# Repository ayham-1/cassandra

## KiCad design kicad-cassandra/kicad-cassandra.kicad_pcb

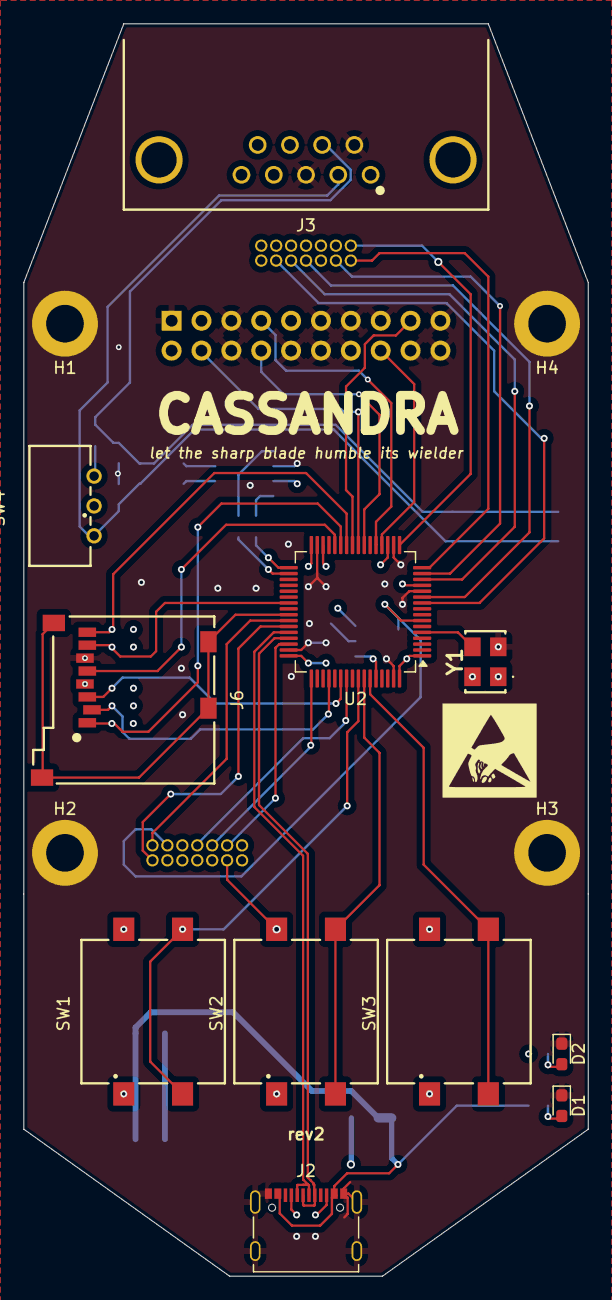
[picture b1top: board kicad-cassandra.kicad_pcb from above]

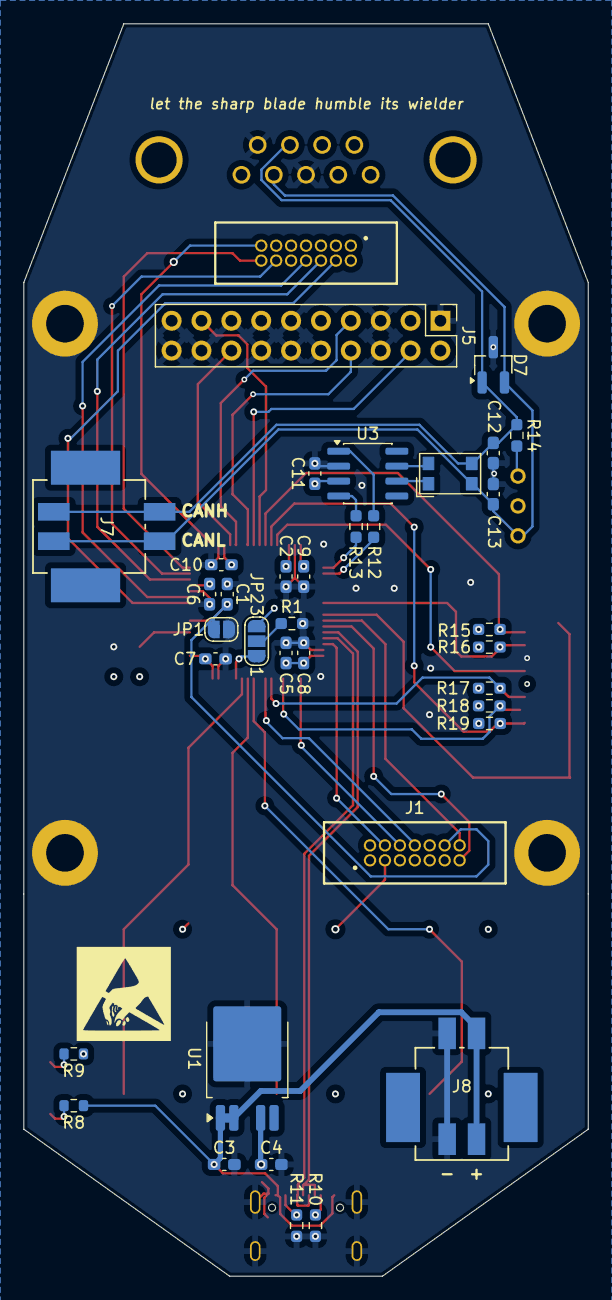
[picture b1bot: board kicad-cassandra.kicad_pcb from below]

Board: 4 copper layers, 48.0 x 106.5 mm, 52 parts (37 on the bottom side), 49 nets.

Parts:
C1, C6, C7, C8, C9, C10, C11: 100n; C_0603_1608Metric_Pad1.08x0.95mm_HandSolder
C2: 2.2u; C_0603_1608Metric_Pad1.08x0.95mm_HandSolder
C3: 1u; C_0603_1608Metric_Pad1.08x0.95mm_HandSolder
C4, C5: 4.7u; C_0603_1608Metric_Pad1.08x0.95mm_HandSolder
C12, C13: 10p; C_0603_1608Metric_Pad1.08x0.95mm_HandSolder
D1, D2: RED; LED_0603_1608Metric_Pad1.05x0.95mm_HandSolder
D7: SZNUP2105L; SOT-23_Handsoldering
H1, H2, H3, H4: MountingHole_Pad; MountingHole_3.2mm_M3_DIN965_Pad
J1, J4: Conn_ST_STDC14; ST_Link_Connection
J2: USB_C_Receptacle_USB2.0_16P; USB_C_Receptacle_Palconn_UTC16-G
J3: DE9_Pins_MountingHoles; WE-D-SUB_THT90_EC_210112013
J5: Conn_02x10_Odd_Even; PinHeader_2x10_P2.54mm_Vertical
J6: Micro_SD_Card_Det1; 693071010811
J7, J8: CONN4_05010302_WRE
JP1: SolderJumper_2_Open; SolderJumper-2_P1.3mm_Open_RoundedPad1.0x1.5mm
JP2: SolderJumper_3_Open; SolderJumper-3_P1.3mm_Open_RoundedPad1.0x1.5mm_NumberLabels
L1: 744235510; L_CommonModeChoke_Coilcraft_1812CAN
R1, R15, R16, R17, R18, R19: 10k; R_0603_1608Metric_Pad0.98x0.95mm_HandSolder
R8: 330; R_0603_1608Metric
R9: 230; R_0603_1608Metric
R10, R11: 5.1k; R_0603_1608Metric_Pad0.98x0.95mm_HandSolder
R12, R13: 4.7k; R_0603_1608Metric_Pad0.98x0.95mm_HandSolder
R14: 120; R_0603_1608Metric_Pad0.98x0.95mm_HandSolder
SW1, SW2, SW3: SW_Push; 430162073826
SW4: SW_SPDT; 450302014072
U1: BD33FC0WFP; TO-252-4
U2: STM32F446RETx; LQFP-64_10x10mm_P0.5mm
U3: SN65HVD232; SOIC-8_3.9x4.9mm_P1.27mm
Y1: 831024589

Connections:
+3.3V: C4.1, C5.1, C6.1, C7.1, C8.1, C9.1, C10.1, C11.1, J1.3 (VCC), J5.2, J6.4 (VDD), JP2.3 (B), R9.1, R15.1, R16.1, R17.1, R18.1, R19.1, SW1.1, SW2.1, SW3.1, U1.4 (VO), U2.1 (VBAT), U2.13 (VDDA), U2.19 (VDD), U2.32 (VDD), U2.48 (VDD), U2.64 (VDD), U3.3 (VCC), Y1.1 (ENABLE/DISABLE), Y1.4 (+VS)
/CAN/CAN_HIGH: C12.1, D7.1 (K), J3.7, J7.1, L1.3, R14.1
/CAN/CAN_LOW: C13.2, D7.2 (K), J3.2, J7.2, L1.2, SW4.2 (B)
/CAN/CAN_RX: R13.1, U2.33 (PB12)
/CAN/CAN_TX: R12.1, U2.34 (PB13)
/DISPLAY_ACTIVE_LOW_CHIP_SELECT: J5.17, U2.25 (PC5)
/DISPLAY_ACTIVE_LOW_RESET: J5.16, U2.20 (PA4)
/DISPLAY_DC: J5.4, U2.24 (PC4)
/DISPLAY_SPI_SCLK: J5.7, U2.21 (PA5)
/DISPLAY_SPI_SDIN: J5.8, U2.23 (PA7)
/HOST_RST: C1.1, J1.12 (~RST), JP1.2 (B), U2.7 (NRST)
/HOST_SWCLK: J1.6 (JCLK/SWCLK), U2.49 (PA14)
/HOST_SWDIO: J1.4 (JTMS/SWDIO), U2.46 (PA13)
/HOST_SWO: J1.8 (JTDO/SWO), U2.55 (PB3)
/HOST_VCP_RX: J1.13 (VCP_RX), U2.43 (PA10)
/HOST_VCP_TX: J1.14 (VCP_TX), U2.42 (PA9)
/HSE: U2.5 (PH0), Y1.3 (OUTPUT)
/PBT_0: SW1.2, U2.57 (PB5)
/PBT_1: SW2.2, U2.58 (PB6)
/PBT_2: SW3.2, U2.59 (PB7)
/TGT_RST: J4.12 (~RST), U2.15 (PA1)
/TGT_SWCLK: J4.6 (JCLK/SWCLK), U2.14 (PA0)
/TGT_SWDIO: J4.4 (JTMS/SWDIO), U2.10 (PC2)
/TGT_SWO: J4.8 (JTDO/SWO), U2.11 (PC3)
/TGT_VCP_RX: J4.13 (VCP_RX), U2.17 (PA3)
/TGT_VCP_TX: J4.14 (VCP_TX), U2.16 (PA2)
/USB/USB_D+: J2.A6 (D+), J2.B6 (D+), U2.45 (PA12)
/USB/USB_D-: J2.A7 (D-), J2.B7 (D-), U2.44 (PA11)
/uSD_CLK: J6.5 (CLK), U2.28 (PB2)
/uSD_CMD: J6.3 (CMD), R17.2, U2.54 (PD2)
/uSD_D0: J6.7 (DAT0), R16.2, U2.39 (PC8)
/uSD_D1: J6.8 (DAT1), R15.2, U2.26 (PB0)
/uSD_D2: J6.1 (DAT2), R19.2, U2.27 (PB1)
/uSD_D3: J6.2 (DAT3/CD), R18.2, U2.52 (PC11)
/uSD_DET: J6.9 (DET_B), J6.10 (DET_A), U2.41 (PA8)
GND: C1.2, C2.2, C3.2, C4.2, C5.2, C6.2, C7.2, C8.2, C9.2, C10.2, C11.2, C12.2, C13.1, D1.1 (K), D2.1 (K), D7.3 (A), H1.1, H2.1, H3.1, H4.1, J1.5 (GND), J1.7 (GND), J1.11 (GNDDetect), J2.A1 (GND), J2.A12 (GND), J2.B1 (GND), J2.B12 (GND), J2.S1 (SHIELD), J3.3, J3.6, J4.5 (GND), J4.7 (GND), J4.11 (GNDDetect), J5.1, J5.5, J5.6, J5.10, J5.11, J5.12, J5.13, J5.14, J5.15, J5.18, J5.19, J5.20, J6.6 (VSS), J8.1, JP1.1 (A), R1.2, R10.2, R11.2, U1.3 (GND), U2.12 (VSSA), U2.18 (VSS), U2.31 (VSS), U2.47 (VSS), U2.63 (VSS), U3.2 (GND), Y1.2 (GND)
unnamed: D1.2 (A), R8.2
unnamed: D2.2 (A), R9.2
unnamed: J2.A5 (CC1), R10.1
unnamed: J2.B5 (CC2), R11.1
unnamed: JP2.1 (A), U2.60 (BOOT0)
unnamed: JP2.2 (C), R1.1
unnamed: R14.2, SW4.3 (C)
unnamed: C2.1, U2.30 (VCAP_1)
unnamed: L1.4, U3.7 (CANH)
unnamed: L1.1, U3.6 (CANL)
unnamed: R12.2, U3.1 (D)
unnamed: R13.2, U3.4 (R)
VDD: C3.1, J2.A4 (VBUS), J2.A9 (VBUS), J2.B4 (VBUS), J2.B9 (VBUS), J8.2, R8.1, U1.1 (EN), U1.2 (VCC)

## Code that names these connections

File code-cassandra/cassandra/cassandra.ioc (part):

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Mcu.Name=STM32F446R(C-E)Tx
Mcu.Package=LQFP64
Mcu.UserName=STM32F446RETx
PA0-WKUP.GPIOParameters=GPIO_Label
PA0-WKUP.GPIO_Label=TGT_SWCLK
PA0-WKUP.Signal=S_TIM2_CH1_ETR
PA1.GPIOParameters=GPIO_Label
PA1.GPIO_Label=TGT_RST
PA1.Signal=GPIO_Output
PA10.Mode=Asynchronous
PA10.Signal=USART1_RX
PA11.GPIOParameters=GPIO_PuPd
PA11.GPIO_PuPd=GPIO_PULLUP
PA11.Mode=Device_Only
PA11.Signal=USB_OTG_FS_DM
PA12.GPIOParameters=GPIO_PuPd
PA12.GPIO_PuPd=GPIO_PULLUP
PA12.Mode=Device_Only
PA12.Signal=USB_OTG_FS_DP
PA13.Mode=Serial_Wire
PA13.Signal=SYS_JTMS-SWDIO
PA14.Mode=Serial_Wire
PA14.Signal=SYS_JTCK-SWCLK
PA2.Mode=Asynchronous
PA2.Signal=USART2_TX
PA3.Mode=Asynchronous
PA3.Signal=USART2_RX
PA4.GPIOParameters=GPIO_PuPd,GPIO_Label
PA4.GPIO_Label=DISPLAY_ACTIVE_LOW_RESET
PA4.GPIO_PuPd=GPIO_PULLUP
PA4.Signal=GPIO_Output
PA5.Mode=Full_Duplex_Master
PA5.Signal=SPI1_SCK
PA6.Mode=Full_Duplex_Master
PA6.Signal=SPI1_MISO
PA7.Mode=Full_Duplex_Master
PA7.Signal=SPI1_MOSI
PA8.GPIOParameters=GPIO_Label
PA8.GPIO_Label=uSD_DET
PA8.Signal=GPIO_Input
PA9.Mode=Asynchronous
PA9.Signal=USART1_TX
PB0.GPIOParameters=GPIO_PuPd
PB0.GPIO_PuPd=GPIO_PULLUP
PB0.Mode=SD_4_bits_Wide_bus
PB0.Signal=SDIO_D1
PB1.GPIOParameters=GPIO_PuPd
PB1.GPIO_PuPd=GPIO_PULLUP
PB1.Mode=SD_4_bits_Wide_bus
PB1.Signal=SDIO_D2
PB12.GPIOParameters=GPIO_PuPd
PB12.GPIO_PuPd=GPIO_PULLUP
PB12.Mode=CAN_Activate
PB12.Signal=CAN2_RX
PB13.Mode=CAN_Activate
PB13.Signal=CAN2_TX
PB2.GPIOParameters=GPIO_PuPd
PB2.GPIO_PuPd=GPIO_NOPULL
PB2.Mode=SD_4_bits_Wide_bus
PB2.Signal=SDIO_CK
PB5.GPIOParameters=GPIO_PuPd,GPIO_Label,GPIO_ModeDefaultEXTI
PB5.GPIO_Label=PBT_0
PB5.GPIO_ModeDefaultEXTI=GPIO_MODE_IT_FALLING
PB5.GPIO_PuPd=GPIO_PULLDOWN
PB5.Signal=GPXTI5
PB6.GPIOParameters=GPIO_PuPd,GPIO_Label,GPIO_ModeDefaultEXTI
PB6.GPIO_Label=PBT_1
PB6.GPIO_ModeDefaultEXTI=GPIO_MODE_IT_FALLING
PB6.GPIO_PuPd=GPIO_PULLDOWN
PB6.Signal=GPXTI6
PB7.GPIOParameters=GPIO_PuPd,GPIO_Label
PB7.GPIO_Label=PBT_2
PB7.GPIO_PuPd=GPIO_PULLDOWN
PB7.Signal=GPXTI7
PC11.GPIOParameters=GPIO_PuPd
PC11.GPIO_PuPd=GPIO_PULLUP
PC11.Mode=SD_4_bits_Wide_bus
PC11.Signal=SDIO_D3
PC2.GPIOParameters=GPIO_Label
PC2.GPIO_Label=TGT_SWDIO
PC2.Signal=GPIO_Output
PC3.GPIOParameters=GPIO_Label
PC3.GPIO_Label=TGT_SWO
PC3.Signal=GPIO_Output
PC4.GPIOParameters=GPIO_Label
PC4.GPIO_Label=DISPLAY_DC
PC4.Signal=GPIO_Output
PC5.GPIOParameters=GPIO_PuPd,GPIO_Label
PC5.GPIO_Label=DISPLAY_ACTIVE_LOW_CS
PC5.GPIO_PuPd=GPIO_PULLDOWN
PC5.Signal=GPIO_Output
PC8.GPIOParameters=GPIO_PuPd
PC8.GPIO_PuPd=GPIO_PULLUP
PC8.Mode=SD_4_bits_Wide_bus
PC8.Signal=SDIO_D0
PD2.Mode=SD_4_bits_Wide_bus
PD2.Signal=SDIO_CMD
PH0-OSC_IN.Mode=HSE-External-Clock-Source
PH0-OSC_IN.Signal=RCC_OSC_IN
PH1-OSC_OUT.Mode=HSE-External-Clock-Source
PH1-OSC_OUT.Signal=RCC_OSC_OUT
RCC.HSE_VALUE=50000000
RCC.SYSCLKFreq_VALUE=72000000
RCC.SYSCLKSource=RCC_SYSCLKSOURCE_PLLCLK
board=custom

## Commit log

2026-04-01 initial
2026-04-01 fix initial
2026-04-01 make sure usb works
2026-04-01 use rohm ldo
2026-04-01 make libumdr compatible
2026-04-02 configure display
2026-04-16 add wire only possibility
2026-04-17 get sdcard working and begin thinking about architecture
2026-04-17 libumdr update
2026-04-18 fix meta
2026-04-18 fix 3d model
2026-04-18 do some freecad stuff
2026-04-19 aligned display with pcb
2026-04-19 make lower shell constraint
2026-04-20 add buttons cad & do binder sketch
2026-04-20 some more cad stuff
2026-04-20 cad: add m3 holes for lower shell
2026-04-20 cad: add canbus extrusion
2026-04-20 cad: left side pocket
2026-04-20 cad: wires in cutouts
2026-04-20 cad: size the mounting holes to MS3S from ruthex
2026-04-20 cad: fix canbus connection
2026-04-22 cad: attempt fix ports and chamfer stuff
2026-04-22 add display 10x2 connector
